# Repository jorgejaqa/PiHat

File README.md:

# PiHat
Raspberry Pi Automation HAT 5 Relays, 8 optocouplers, 24vac power supply, and more

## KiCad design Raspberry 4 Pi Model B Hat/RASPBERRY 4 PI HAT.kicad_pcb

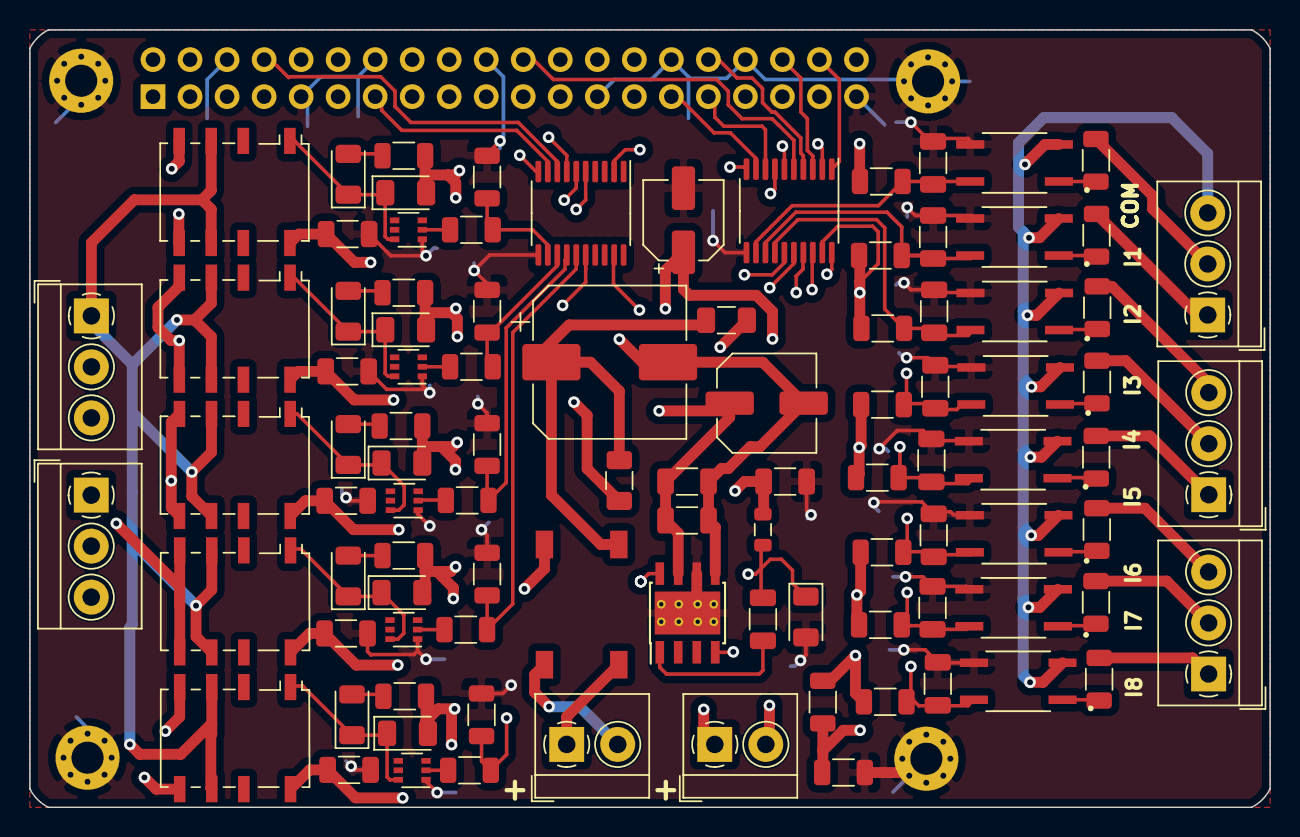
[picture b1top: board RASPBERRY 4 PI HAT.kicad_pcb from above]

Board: 4 copper layers, 85.1 x 53.3 mm, 101 parts (1 on the bottom side), 76 nets.

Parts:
C1, C2, C3, C4, C5, C6, C7, C8: 100nF; C_1206_3216Metric
C9: 270uF; CP_Elec_10x10
C10, C13, C17, C18, C19, C20: 10uF; C_1206_3216Metric
C11, C15: 4.7uF; C_1206_3216Metric
C12: 0.01uF; C_1206_3216Metric
C14: 220uF; CP_Elec_5x5.9
C16: 47uF; C_Elec_6.3x5.8
D1: B340; D_1206_3216Metric
D2, D3, D5, D10, D11: DIODE; D_1206_3216Metric
D6, D7, D8, D9, D14: LED; LED_1206_3216Metric
DB107S1: DB107S; DIOB_DB107S
F1, F2: 1A; Fuse_1206_3216Metric
H1, H2, H3, H4: MountingHole_Pad; MountingHole_2.2mm_M2_Pad_Via
J1, J2: Screw_Terminal_01x02; TerminalBlock_4Ucon_1x02_P3.50mm_Horizontal
J3, J4, J5, J6, J8: Screw_Terminal_01x03; TerminalBlock_4Ucon_1x03_P3.50mm_Horizontal
J7: Conn_02x20_Odd_Even; PinSocket_2x20_P2.54mm_Vertical
K1, K2, K3, K4, K5: G6K-2; Relay_DPDT_Omron_G6K-2F-Y
L2: 22uH; L_0805_2012Metric
Q1, Q2, Q3, Q4, Q5: PMBT3904YS; SOT-363_SC-70-6
R1, R2, R3, R4, R5, R6, R7, R8: 1.2K; R_1206_3216Metric
R9, R10, R11, R12, R13, R14, R15, R16: 5K; R_1206_3216Metric
R17, R19, R20, R22, R31, R32: 10K; R_1206_3216Metric
R18: 3.3K; R_1206_3216Metric
R23, R25, R29, R35: 2K; R_1206_3216Metric
R24, R26, R30, R36, R38: 1K; R_1206_3216Metric
R37: 4.7K; R_1206_3216Metric
U1, U3: TXS0108EPW; TSSOP-20_4.4x6.5mm_P0.65mm
U2: TPS5430DDA; TI_SO-PowerPAD-8_ThermalVias
U4, U5, U6, U7, U8, U9, U10, U11: EL817; SOP254P700X200-4N

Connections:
24VDC+: F2.2, J1.1
24VDC-: C9.2, C11.2, C15.2, C16.2, DB107S1.-, J1.2, U2.5
+3V3: J7.1, J7.17, U1.2, U1.10, U3.2, U3.10
+5V: C10.1, C13.1, C14.1, C17.1, C18.1, C19.1, C20.1, D2.2, D3.2, D5.2, D10.2, D11.2, J7.2, J7.4, K1.8, K2.8, K3.8, K4.8, K5.8, L2.2, R9.1, R10.1, R11.1, R12.1, R13.1, R14.1, R15.1, R16.1, R17.1, R23.1, R25.1, R29.1, R35.1, R37.1, U1.19, U3.19
A0: C1.1, R9.2, U1.12, U4.4
A1: C2.1, R10.2, U1.13, U5.4
A2: C3.1, R11.2, U1.14, U6.4
A3: C4.1, R12.2, U1.15, U7.4
A4: C5.1, R13.2, U1.16, U8.4
A5: C6.1, R14.2, U1.17, U9.4
A6: C7.1, R15.2, U1.18, U10.4
A7: C8.1, R16.2, U1.20, U11.4
AC+: DB107S1.~, J2.1
AC-: DB107S1.~., J2.2
COM1: J3.3, U4.2, U5.2, U6.2, U7.2, U8.2, U9.2, U10.2, U11.2
COM2: J6.1, K1.3, K1.6, K2.3, K2.6, K3.3, K3.6, K4.3, K4.6, K5.3, K5.6
GND: C1.2, C2.2, C3.2, C4.2, C5.2, C6.2, C7.2, C8.2, C10.2, C13.2, C14.2, C17.2, C18.2, C19.2, C20.2, D1.2, H1.1, H2.1, H3.1, H4.1, J7.6, J7.9, J7.14, J7.20, J7.25, J7.30, J7.34, J7.39, Q1.1, Q2.1, Q3.1, Q4.1, Q5.1, R18.2, R19.2, R20.2, R22.2, R31.2, R32.2, U1.11, U2.6, U2.9, U3.11, U4.3, U5.3, U6.3, U7.3, U8.3, U9.3, U10.3, U11.3
GPIO3: J7.5, U3.5
GPIO4: J7.7, U3.6
GPIO5: J7.29, U1.9
GPIO6: J7.31, U1.8
GPIO12: J7.32, U1.4
GPIO13: J7.33, U1.7
GPIO14: J7.8, U3.8
GPIO15: J7.10, U3.7
GPIO16: J7.36, U1.3
GPIO20: J7.38, U1.1
GPIO25: J7.22, U1.5
GPIO26: J7.37, U1.6
GPIO27: J7.13, U3.9
I1: J3.2, R1.1
I2: J3.1, R2.1
I3: J4.3, R3.1
I4: J4.2, R4.1
I5: J4.1, R5.1
I6: J5.3, R6.1
I7: J5.2, R7.1
I8: J5.1, R8.1
unnamed: C9.1, DB107S1.+, F1.1, F2.1
unnamed: C11.1, C15.1, C16.1, F1.2, U2.7
unnamed: C12.1, D1.1, L2.1, U2.8
unnamed: C12.2, U2.1
unnamed: D6.2, R23.2
unnamed: D7.2, R25.2
unnamed: D9.2, R29.2
unnamed: D14.2, R35.2
unnamed: D8.2, R37.2
unnamed: Q1.2, R24.2
unnamed: Q2.2, R26.2
unnamed: Q3.2, R38.2
unnamed: Q4.2, R30.2
unnamed: Q5.2, R36.2
unnamed: R1.2, U4.1
unnamed: R2.2, U5.1
unnamed: R3.2, U6.1
unnamed: R4.2, U7.1
unnamed: R5.2, U8.1
unnamed: R6.2, U9.1
unnamed: R7.2, U10.1
unnamed: R8.2, U11.1
RL1: D2.1, D6.1, K1.1, Q1.6
RL2: D3.1, D7.1, K2.1, Q2.6
RL3: D8.1, D11.1, K3.1, Q3.6
RL4: D5.1, D9.1, K4.1, Q4.6
RL5: D10.1, D14.1, K5.1, Q5.6
VS: R17.2, R18.1, U2.4
Y0: R19.1, R24.1, U3.12
Y1: R20.1, R26.1, U3.13
Y2: R32.1, R38.1, U3.14
Y3: R22.1, R30.1, U3.15
Y4: R31.1, R36.1, U3.16
YD1: J6.2, K1.4, K1.5
YD2: J6.3, K2.4, K2.5
YD3: J8.1, K3.4, K3.5
YD4: J8.2, K4.4, K4.5
YD5: J8.3, K5.4, K5.5
